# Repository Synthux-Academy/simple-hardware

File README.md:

# simple-hardware
Thie repository includes components and open source templates for Simple synth boards.

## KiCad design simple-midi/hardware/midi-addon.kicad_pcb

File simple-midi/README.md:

# simple-midi: the Simple MIDI expander

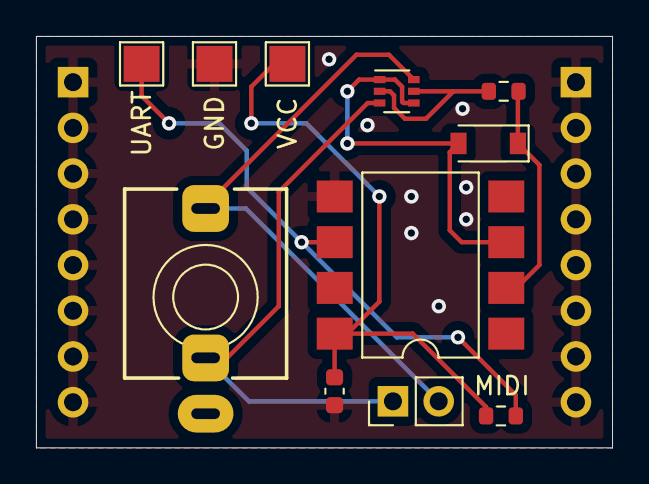
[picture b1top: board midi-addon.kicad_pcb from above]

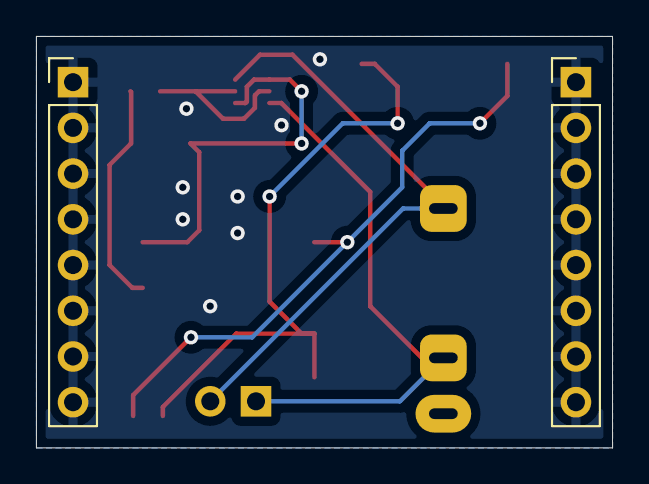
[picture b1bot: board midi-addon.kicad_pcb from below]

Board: 2 copper layers, 32.0 x 22.9 mm, 13 parts (2 on the bottom side), 8 nets.

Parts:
C1: 100n; C_0603_1608Metric
D1: BAT54XY; SOT-363_SC-70-6
D2: 1N4148; D_SOD-123
J1: PJ366ST; Jack_3.5mm_QingPu_WQP-PJ366ST_Vertical
J2: UART; TestPoint_Pad_2.0x2.0mm
J3: GND; TestPoint_Pad_2.0x2.0mm
J4: VCC; TestPoint_Pad_2.0x2.0mm
J5, J6: Conn_01x08; PinHeader_1x08_P2.54mm_Vertical
MIDI: MIDI; PinHeader_1x02_P2.54mm_Vertical
R1: 220R; R_0603_1608Metric
R2: 10k; R_0603_1608Metric
U1: 6N137; SMDIP-8_W9.53mm

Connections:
+3V3: C1.1, J4.1, R2.2, U1.8 (VCC)
/uart: J2.1, R2.1, U1.6 (VO)
GND: C1.2, J3.1, J5.1, J5.2, J5.3, J5.4, J5.5, J5.6, J5.7, J5.8, J6.1, J6.2, J6.3, J6.4, J6.5, J6.6, J6.7, J6.8, U1.5 (GND)
unnamed: D1.1 (anode_1), D1.4 (anode4), D2.2 (A), U1.3 (C)
unnamed: D1.2 (cathode_2), D1.5 (cathode3), R1.2
unnamed: D1.3 (anode3/cathode4), J1.R, MIDI.1
unnamed: D1.6 (cathode1/anode2), J1.T, MIDI.2
unnamed: D2.1 (K), R1.1, U1.2 (A)

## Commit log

2024-01-21 Add content
2024-01-23 Add submodule
